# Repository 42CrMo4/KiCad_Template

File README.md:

# KiCad_Template

This is a template repo for KiCAD v8 projects with 

### Goal & Status
| undefined                             | learn                                                                                            | prototype                  | 80-20-rule                                                   | polished Product |
|---------------------------------------|--------------------------------------------------------------------------------------------------|----------------------------|--------------------------------------------------------------|------------------|
| not known what the project will bring | personally learn something new (function, design, process) otherwise no usefull outcome expected | a working prototype or mvp | 80% outcome with 20% effort. Dont expect a finished product. | -                |

| idea                   | design                                                | implementation | testing | finished |
|------------------------|-------------------------------------------------------|----------------|---------|----------|
| brainstorming workflow | putting together a goal list, architecture, hig level | schematic, pcb |         |          |

## Todo

* ~add DRC, ERC as seperate WF~ 
* ~add DRC, ERC to release WF as blocking~
* ~add release checklist~
* order release checklist
* ~add workflow to automatically create new realease checklist and realease note file and reset the generic for the next release~
* ~Rename artefacts with project name and date?~
* Add diffrent PCB manufactures output via kibot
* ~Update to kicad6_auto:1.3.0~
* use version number for template

## Usage

hit "use this template" button
delet all unneded files in Doc folder
delet all Schematic stuff but not the text Placeholders <<...>>
delet all PCB stuff but not the text Placeholders <<...>> and the Board Edge (or the iBOM will fail). You can remodel it later.

### Workflow
If not working:
setting -> action -> general -> Workflow permissions -> Read and write permissions

## working

in the first workflow run the action will create a new branch "documentation" to store the newest PCBdraw pictures. 
Each action run will force push the png to this branch. So so not use the Fabrication folder in the documentation branch.

## Description. 

| Font                                                                    | Back                                                                      |
|-------------------------------------------------------------------------|---------------------------------------------------------------------------|
|  |  |

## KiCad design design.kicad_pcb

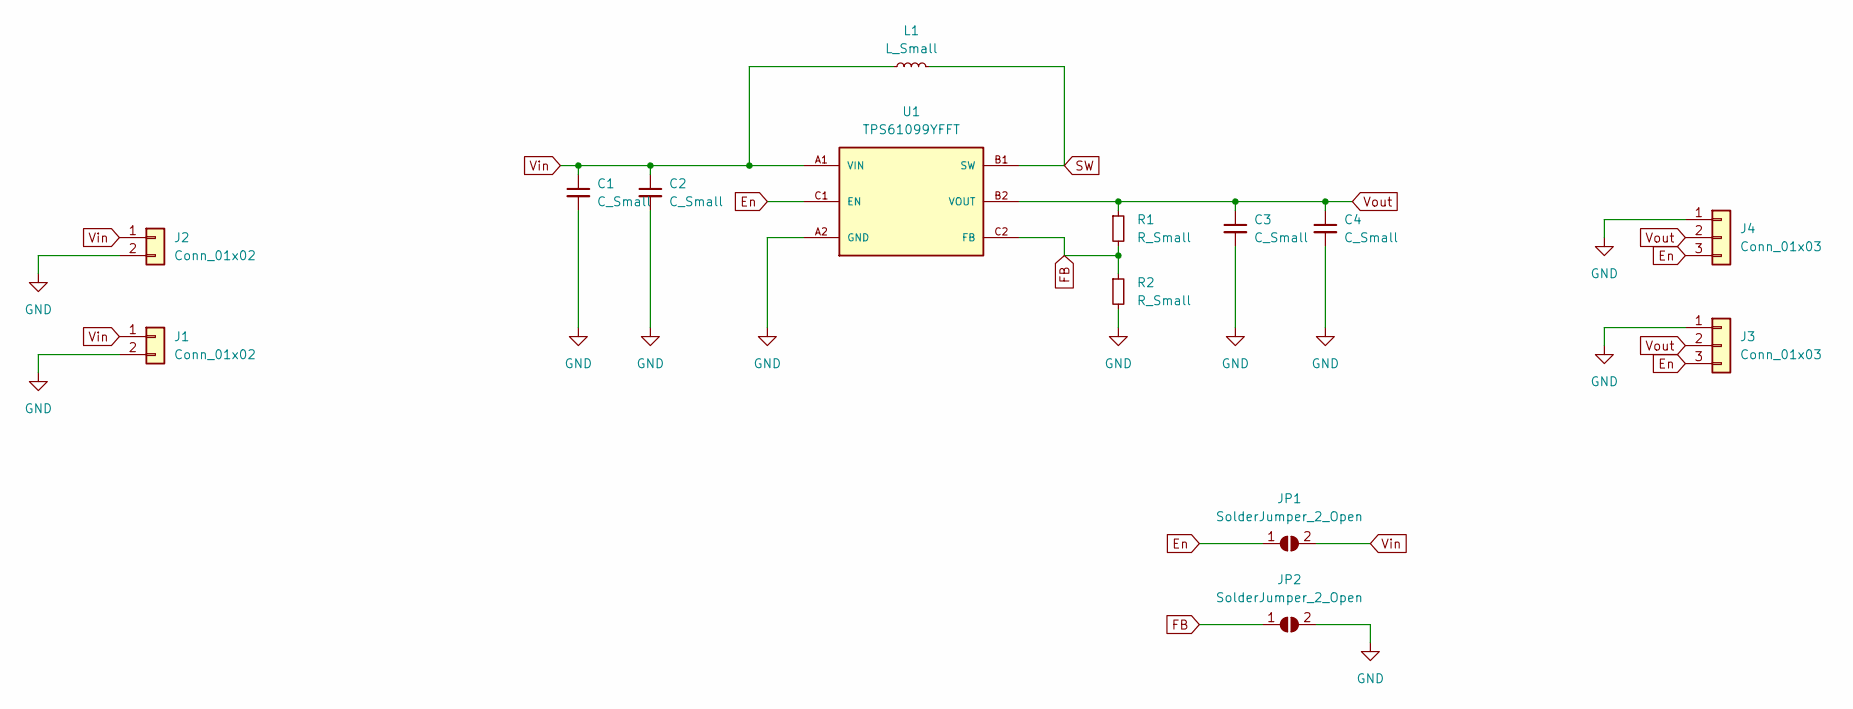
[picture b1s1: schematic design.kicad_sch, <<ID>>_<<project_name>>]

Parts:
C1, C2, C3, C4: C_Small; C_0805_2012Metric
J1, J2: Conn_01x02; PinHeader_1x02_P2.54mm_Vertical
J3, J4: Conn_01x03; PinHeader_1x03_P2.54mm_Vertical
JP1, JP2: SolderJumper_2_Open; SolderJumper-2_P1.3mm_Open_RoundedPad1.0x1.5mm
L1: L_Small; L_1008_2520Metric
R1, R2: R_Small; R_0805_2012Metric
U1: TPS61099YFFT; BGA6N40P3X2_122X88X62N; PARTREV K

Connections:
En: J3.3, J4.3, JP1.1 (A), U1.C1 (EN)
FB: JP2.1 (A), R1.2, R2.1, U1.C2 (FB)
GND: C1.2, C2.2, C3.2, C4.2, J1.2, J2.2, J3.1, J4.1, JP2.2 (B), R2.2, U1.A2 (GND)
SW: L1.2, U1.B1 (SW)
Vin: C1.1, C2.1, J1.1, J2.1, JP1.2 (B), L1.1, U1.A1 (VIN)
Vout: C3.1, C4.1, J3.2, J4.2, R1.1, U1.B2 (VOUT)

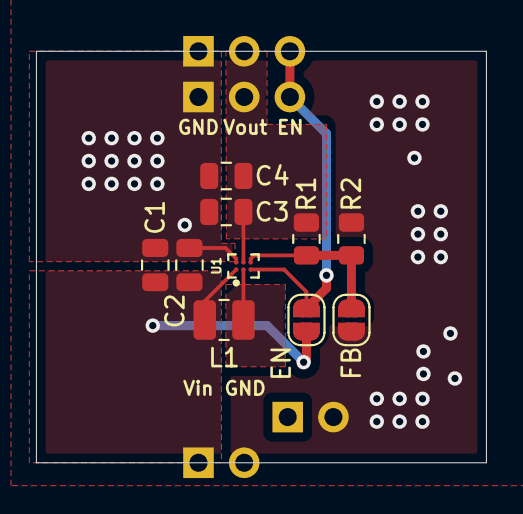
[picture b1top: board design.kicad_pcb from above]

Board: 2 copper layers, 25.0 x 22.9 mm, 14 parts (0 on the bottom side), 6 nets.

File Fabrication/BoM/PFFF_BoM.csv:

Row,Description,Part,References,Value,Footprint,Quantity Per PCB,Status,Datasheet,STANDARD,PARTREV,MAXIMUM_PACKAGE_HEIGHT,MANUFACTURER
1,,C_Small,C1 C2 C3 C4,C_Small,C_0805_2012Metric,4, ,~,,,,
2,,Conn_01x02,J1 J2,Conn_01x02,PinHeader_1x02_P2.54mm_Vertical,2, ,~,,,,
3,,Conn_01x03,J3 J4,Conn_01x03,PinHeader_1x03_P2.54mm_Vertical,2, ,~,,,,
4,,L_Small,L1,L_Small,L_1008_2520Metric,1, ,~,,,,
5,,R_Small,R1 R2,R_Small,R_0805_2012Metric,2, ,~,,,,
6,,TPS61099YFFT,U1,TPS61099YFFT,BGA6N40P3X2_122X88X62N,1, ,,IPC 7351B,K,0.625mm,Texas Instruments

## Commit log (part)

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2022-04-22 WF Raw renaming & uploading after generation
2022-04-22 ADD ID to SCH&PCB Page
2022-04-22 Update Bom and PCB_top
2022-04-22 DEL unneeded checkboxes
2022-04-22 WF Add Archive & Renew Release Docs
2022-04-22 WF update & install git not needed
2022-04-22 WF Add Checkout Step
2022-04-22 WF Typo
2022-04-22 WF Release only on main and commit on main
2022-04-22 WF revert releasing on main branch commit
2022-04-22 Archive & Renew release docs
2022-04-23 WF exit release wf if not on main branch
2022-04-24 ADD table for pics
2022-04-24 Remove trailing space of id:
2022-04-24 ADD pic table & check done ToDos
2022-04-24 ADD ToDo
2022-04-24 Use proper heading
2022-04-24 Use global sed (replacement) option
2022-04-24 use global sed option
2022-04-24 WF Del check branch on release
2022-04-25 make website Link a placeholder
2022-04-29 KP/WF Add 3dview option
2022-04-29 KP use root folder
2022-04-29 KP 3dview was after comment
2022-05-07 add usage
2022-09-27 checkout to v3
2022-09-27 fetch checkout depth
2022-09-27 test change for kibot diff
2022-09-27 test change for kibot diff 2
2022-09-29 diff sch
2022-09-29 change to pcb_print
2022-10-02 Squashed commit of the following:
    commit 55542e7a8053af1b9a33b06374088349c7da5968
    Author: 42CrMo4 <44754810+42CrMo4@users.noreply.github.com>
    Date: Thu Sep 29 21:47:52 2022 +0200
    change to pcb_print
2022-10-02 change to pcb_print (#1)
2022-10-02 Change to ghcr and kicad6_auto:1.3.0
2022-10-02 add page option
2022-10-02 Revert "Squashed commit of the following:"
    This reverts commit 65fa065b35e3541c0d392757ebdcd858b856efa4.
2022-10-02 add todos
2022-10-02 Kicad6_auto pin to v1.3.0 (#2)
    * Change to ghcr and kicad6_auto:1.3.0
    * Change to ghcr and kicad6_auto:1.3.0
2022-10-02 update todos
2022-10-02 remove unused kibot option
2022-10-02 reorganization
2022-10-02 Kibot options tidyup (#3)
    * remove unused kibot option
    * reorganization
    * Update Bom and PCB_top
2022-10-03 find last tag and use it for diff
2022-10-03 make diff name no viariable
2022-10-03 add correct kibot action names
2022-10-03 typo
2022-10-08 how to find the last tag
2022-10-26 add comment about whitespace in project name
2022-10-26 Add Template first Steps
2022-10-26 update to Kibot 1.4.0 (#4)
2022-10-26 add diff condition ToDos
2022-10-26 Revert Diff PCB action to KIBOT_LAST-1
2022-10-26 Revert Diff PCB action to KIBOT_LAST-1 (#5)
    * Revert Diff PCB action to KIBOT_LAST-1
    * Update Bom and PCB_top
2022-10-26 Change comment to own line
2022-10-26 Add project.properties to event
2022-10-26 exclude read comments from properties file
2022-10-26 Add comment
2022-11-28 use checkout v3
2022-12-15 get the documentation to another branch
2022-12-15 test change for action trigger
2022-12-15 another change for action test
2022-12-15 revert test changes
2022-12-15 add force push
2022-12-15 ignore comments in properties file
2022-12-15 test change for workflow
2022-12-15 change sequence of ignore
2022-12-22 add cvs BOM as artefact
2022-12-22 also upload the csv to release
2022-12-22 another try to upload cvs BOM
2022-12-22 update to checkout v3
2022-12-22 update to checkout v3 (#6)
2022-12-22 use Kibot v1.5.1
2022-12-22 use Kibot v1.5.1 (#7)
2022-12-22 rename and shorten BoM for release
2022-12-22 csv again
2022-12-22 use vimtor/action-zip@v1.1
2022-12-22 use vimtor/action-zip@v1.1 (#8)
2022-12-22 tipo missing space " "
2023-09-20 Add project status and Goal definition table
2023-11-12 PCB add another variable text block
    makes deleting stuff easier if starting from this template. No need to deselect the variable text block on the pcb.
2024-02-19 on: workflow_call:
2024-02-19 add on workflow_call:
2024-02-19 use external Workflows
2024-02-19 add via
2024-03-03 add diff for tag
2024-03-05 diff by tag
2024-03-05 use the correct naming variable
2024-03-05 add pdf extension
2024-03-05 what happends if removed?
2024-03-05 not valid Tag?
2024-03-05 fake change
2024-03-06 fake change - comment
2024-03-08 use kicad 8 branch
2024-03-27 save in kicad 8
2024-03-27 fake cahnge
2024-03-28 auto zoom 3d view
2024-03-30 add navigate_results output
2024-03-30 navigate_results fix
2024-03-30 remove navigate_results
2024-03-30 Revert "fake change"
    This reverts commit 53b6625fe8b0224a7cb3863a905f883249e6ca34.
2024-03-31 add kiplot outputs
2024-03-31 fix spelling
2024-04-04 refine kiplot output with directories and a width
2024-04-04 add global dir
2024-04-04 add default names
2024-04-04 fix default dir?
2024-04-04 add gerber dir
2024-04-04 remove 3d render width
2024-04-04 remove blender export
2024-04-04 remove global dir
2024-04-04 add dir for kicanvas
2024-04-04 fix global name
2024-04-04 dir for Diffs
2024-04-04 no project kicanvas
2024-04-04 no output names
2024-04-04 grouping
2024-04-04 ad 3d render top?
2024-04-14 use v6.0 tag as workflow
2024-04-14 remove preflight section
2024-04-14 add preflights again
2024-04-14 use new erc, drc options
2024-04-14 report erc, drc
2024-04-14 fix formating
2024-04-14 like this?
2024-04-14 dont stop erc and drc
2024-04-14 remove naming from BOM output
2024-04-14 remove TAG Diff option for now
2024-04-14 add kibom
2024-04-14 remove kibom and hide project infos in bom output
2024-04-14 formation?
2024-04-14 formating agian
2024-04-14 change Deprecated pdf_pcb_print output
2024-04-14 adapt to new option
2024-04-14 format again
2024-04-14 format
2024-04-15 add jlcpcb zip output
2024-04-15 refine jlcpcb
2024-04-15 remove jlcpxb specific, add PCBway
2024-04-15 temporaly use all branches for bom upload and render
2024-04-15 Revert "fake change"
    This reverts commit 0a7a278205bd20c142261591d5de84e048c54d08.
2024-04-15 Revert "fake change"
    This reverts commit 5009e6975f5137ac1bf25631ed6b11a1b2671252.
2024-04-28 Revert "fake change"
    This reverts commit 55987b273313369e49f7260e157a0ffda1239707.
2024-05-26 change Goal to checklist, remove Status
2024-05-30 use Diff_add branch
2024-05-30 Revert "fake change"
    This reverts commit dd915477e0885dab546d5bbc139372ed1afc3f9e.
2024-05-30 Reapply "fake change"
    This reverts commit b98ccb4ebc537023de1b764ba469f76477730565.
2024-05-30 Revert "Reapply "fake change""
    This reverts commit ab27b7ad507b12a5792f6427d9ced38c82334a62.
2024-05-30 fake
2024-05-30 Revert "fake"
    This reverts commit faa94412f01bbde9db05aeb031553acbff5e806a.
2024-05-30 Reapply "fake"
    This reverts commit 69fef439441310a1665b90a83208c40ce9d405da.
2024-05-30 Revert "Reapply "fake""
    This reverts commit aa1c37b4647d8c92e16edf24fc3d876cecc8e17b.
2024-05-31 change to root
2024-05-31 Revert "fake change"
    This reverts commit 2c2b21bc17470d50bac0025b0b31d4ad69f78a2e.
2024-05-31 Reapply "fake change"
    This reverts commit 2de747658013c157f2b78e3804b3571b08e2b310.
2024-06-01 add in the workflow to make it easier.
2024-06-01 remove unneded
2024-06-01 add 3d Blender render
2024-06-01 Revert "Update generate_output.yml"
    This reverts commit 798374012091400bd1f89f4e197670b27a3a007a.
2024-06-01 dont use the ID prefix
2024-06-01 remove unneeded
2024-06-01 use ID instead of design
2024-06-01 update name
2024-06-01 update to v8
2024-06-02 change name to config.kiplot.yaml
2024-06-02 use curl to fetch Diff_append
2024-06-02 del unneeded
2024-07-05 update broken link
2024-07-05 restructure
2024-07-05 Revert "restructure"
    This reverts commit 2061fe56b09e988dfc5a7052f433498e5d6c333d.
2024-07-05 add description properties
2024-07-05 DEL Fabrication folder
2024-07-06 DEL Docs
2024-07-06 Add license
2024-07-06 cange file name
2024-07-06 Revert "cange file name"
    This reverts commit e51ba2040720717c6ed0ead182a27751e767c7ab.
2024-07-06 only run workflow manualy
2024-07-06 Revert "DEL Docs"
    This reverts commit d4789f3b469f1a2d48d680a31b348f9557dc35f3.
2024-07-06 combine rc and release workflow.
2024-07-06 comment out 3D blender and DIFF
2024-07-06 combine workflows
2024-07-06 also use push events
2024-07-06 DEL Stencil
2024-07-06 use diff, debug, del gerber
2024-07-06 syntax
2024-07-06 syntax again
2024-07-07 syntax error
2024-07-07 change variable names
2024-10-05 move to python tag list - step1
2024-10-05 wrong kicanvas option?
2024-11-04 Add KiCad 3D Model Checker
2024-11-04 fake add component
2024-11-04 Revert "Create BM04B-SRSS-TB_LF__SN_.step"
    This reverts commit 0729f527616381e3bdd23a72c6194f84ca1e9b0a.
2024-11-04 Revert "fake add component"
    This reverts commit 96a2ccfc30ab2f58efbd566c060a8c6ea30395aa.
2025-03-18 update Kicad Files to KiCadv9
2025-03-18 Revert "fake change"
    This reverts commit 08dd532ad594e6d1b282230bba7f8d1e4472d9f5.
2025-03-18 use all branches for update_bom_pcbtop.yml
2025-03-18 do not use zoom in 3d
    should enable auto zoom
